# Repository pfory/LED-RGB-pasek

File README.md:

https://github.com/corbanmailloux/esp-mqtt-rgb-led

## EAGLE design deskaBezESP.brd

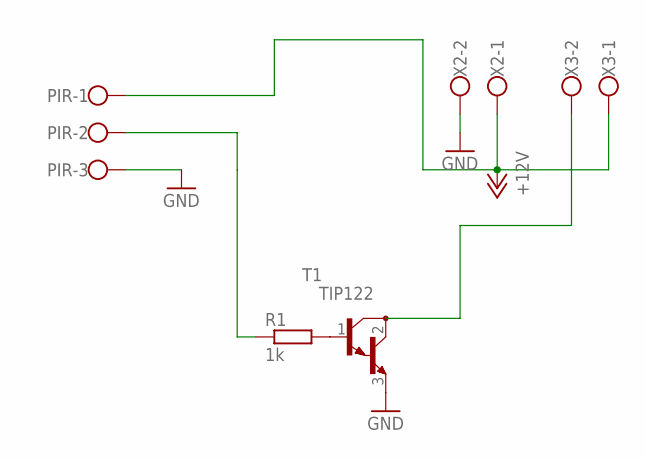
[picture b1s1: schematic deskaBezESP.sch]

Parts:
PIR: W237-103
R1: 1k; 0207/10
T1: TIP122; TO220
X2, X3: W237-102

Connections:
+12V: PIR.1, X2.1, X3.1
GND: PIR.3, T1.3 (E), X2.2
unnamed: T1.2 (C), X3.2
unnamed: R1.2, T1.1 (B)
PIROUT: PIR.2, R1.1

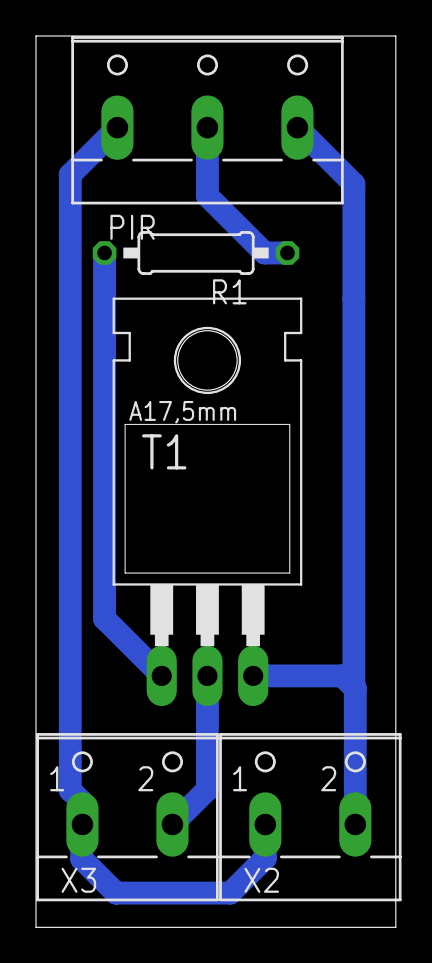
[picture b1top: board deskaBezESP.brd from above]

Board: 2 copper layers, 20.0 x 49.5 mm, 5 parts (0 on the bottom side), 5 nets.

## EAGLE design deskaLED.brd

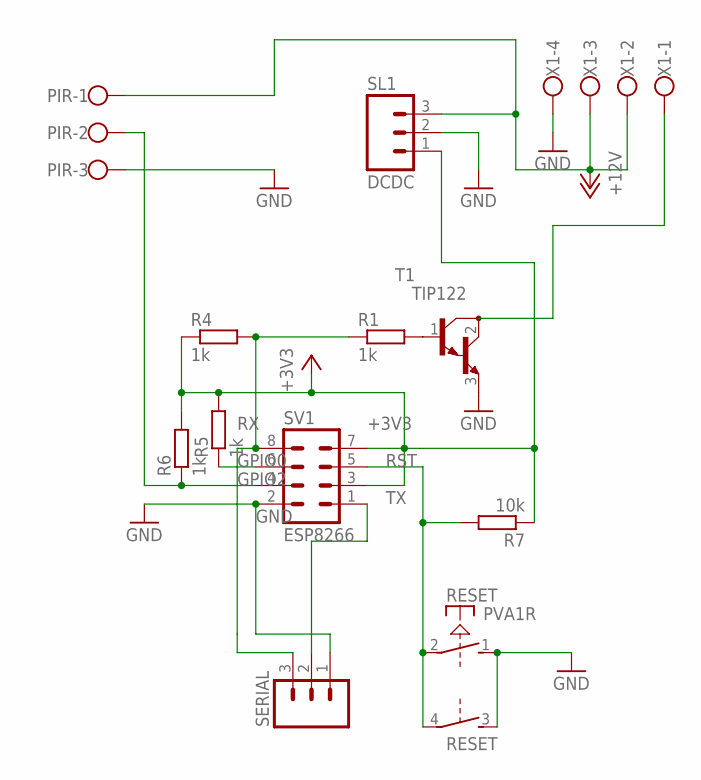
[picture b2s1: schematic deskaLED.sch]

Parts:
PIR: W237-103
R1, R4, R5, R6: 1k; 0207/10
R7: 10k; 0207/10
RESET: PVA1R
SERIAL: M03; 03P
SL1: DCDC; 03P
SV1: ESP8266; MA04-2
T1: TIP122; TO220
X1: W237-4

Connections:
+3V3: R4.1, R5.2, R6.2, R7.1, SL1.1, SV1.3, SV1.7
+12V: PIR.1, SL1.3, X1.2, X1.3
GND: PIR.3, RESET.1 (S), RESET.3 (S), SERIAL.1, SL1.2, SV1.2, T1.3 (E), X1.4
GPIO0: R5.1, SV1.6
GPIO2: PIR.2, R6.1, SV1.4
unnamed: T1.2 (C), X1.1
unnamed: R1.2, T1.1 (B)
RST: R7.2, RESET.2, RESET.4, SV1.5
RX: R1.1, R4.2, SERIAL.3, SV1.8
TX: SERIAL.2, SV1.1

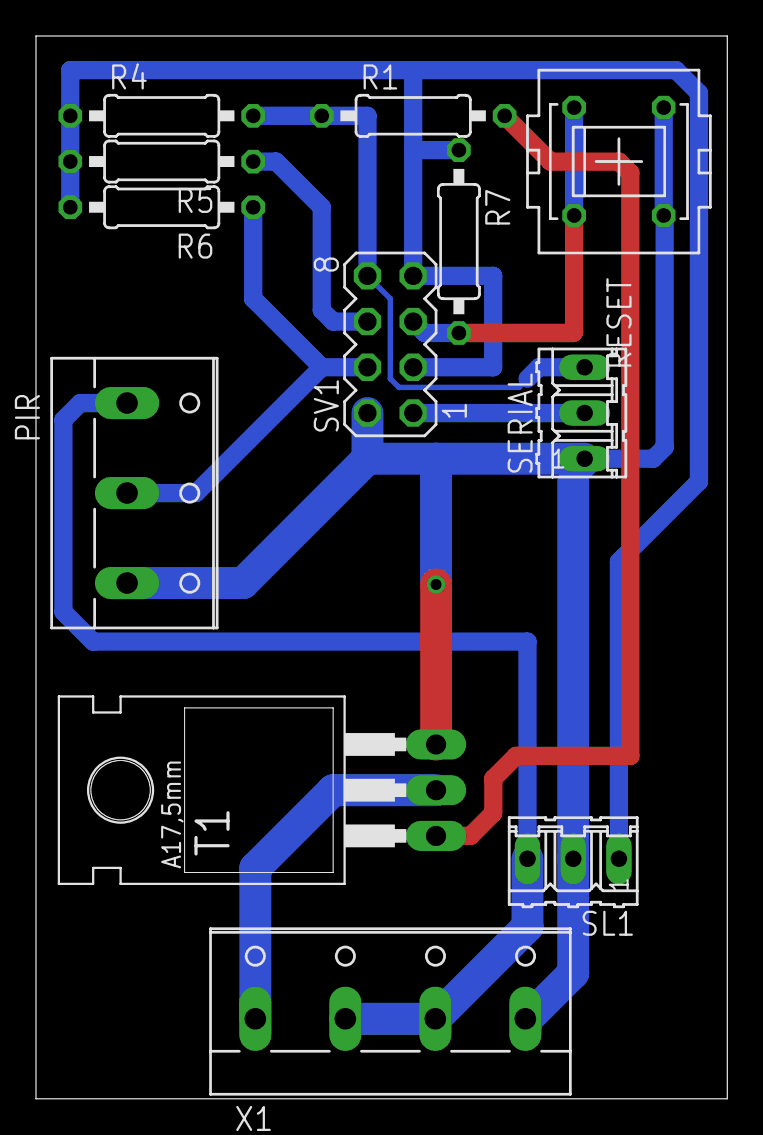
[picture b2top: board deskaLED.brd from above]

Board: 2 copper layers, 38.4 x 59.0 mm, 12 parts (0 on the bottom side), 10 nets.

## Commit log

2017-11-28 inital
2017-11-28 verze ESP8266-01
2017-11-28 add readme
2017-12-06 zmeny plosnaku
2018-09-24 uprava desky
2018-09-24 upravy desky
2018-09-25 deska
2018-09-25 +test
2018-09-26 zmena odporu
2018-10-30 upravy desku - popisky
2019-11-07 redesign aplikace
2021-06-30 prejmenovani
2021-07-07 verze
2021-09-02 zmena formatu json zpravy
